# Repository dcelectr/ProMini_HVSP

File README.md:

# ProMini_HVSP
High voltage serial programer to set the RSTDISBL fuse for the [ATiny SD Audio Player](https://github.com/dcelectr/ATtiny85_SD_Audio_Player) (Stereo, OSC, and Mono-HR versions).

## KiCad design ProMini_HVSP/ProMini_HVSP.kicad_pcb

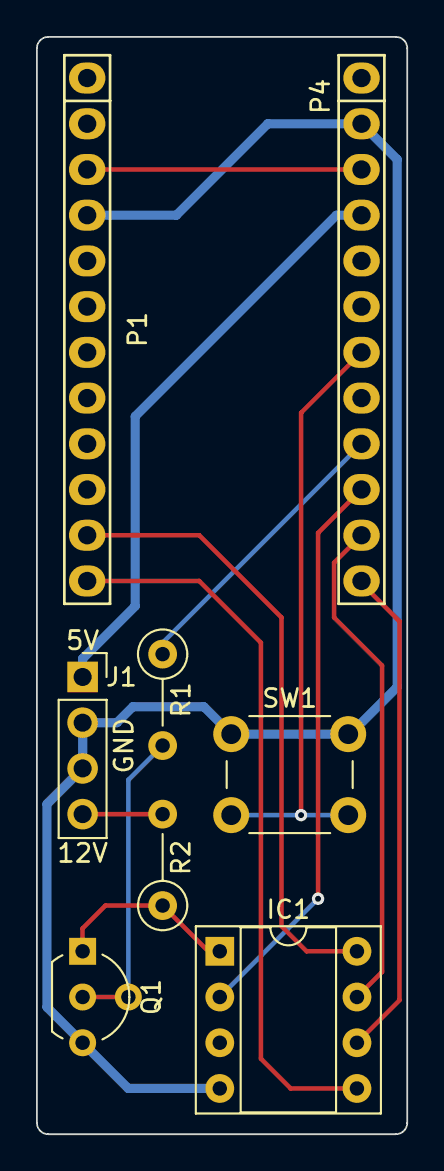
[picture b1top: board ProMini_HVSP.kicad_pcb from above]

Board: 2 copper layers, 20.6 x 61.0 mm, 9 parts (0 on the bottom side), 13 nets.

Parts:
IC1: DIL8S; DIP-8_W7.62mm_Socket
J1: 12V_Regulator module; PinSocket_1x04_P2.54mm_Vertical
P1: GND; PAD
P1#2: Digital; Socket_Strip_Arduino_1x12
P4: Analog; Socket_Strip_Arduino_1x12
Q1: BC547; TO-92L_Inline_Wide
R1, R2: 1k; R_Axial_DIN0207_L6.3mm_D2.5mm_P5.08mm_Vertical
SW1: READY; SW_PUSH_6mm

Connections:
/8: IC1.8, P1#2.11
/9: IC1.5, P1#2.12
/10: IC1.6, P4.12
/11: IC1.7, P4.11
/12: IC1.2, P4.10
/13: P4.9, R1.1
/A1: P4.7, SW1.2
/Reset: P1#2.3, P4.3
/V+12: IC1.1, Q1.1, R2.1
GND: IC1.4, J1.2, J1.3, P1#2.4, P4.2, Q1.3, SW1.1
unnamed: J1.4, R2.2
unnamed: P1.1, Q1.2, R1.2
VCC: J1.1, P4.4
